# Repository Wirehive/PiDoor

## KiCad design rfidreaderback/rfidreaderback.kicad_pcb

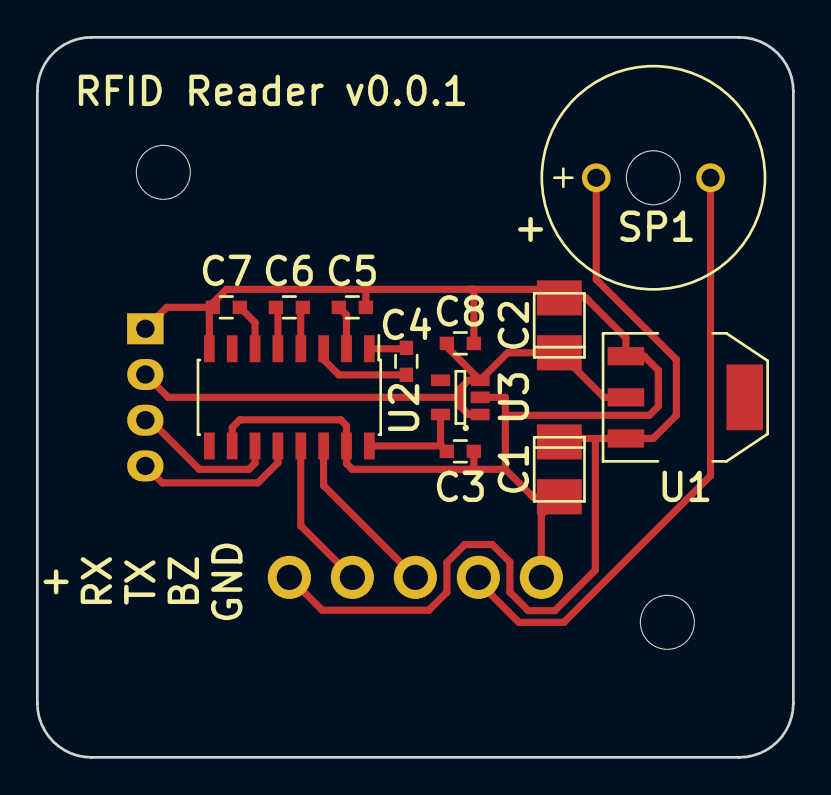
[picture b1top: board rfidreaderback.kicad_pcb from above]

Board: 2 copper layers, 42.0 x 40.0 mm, 14 parts (1 on the bottom side), 15 nets.

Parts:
C1, C2: 22µ; TantalC_SizeT_EIA-3528
C3, C4, C5, C6, C7, C8: 1µ; C_0603
P1: READER; Socket_Strip_Straight_1x04
P2: PI; 3_5mm_terminal_1x05
SP1: MCABI-020-RC; MagneticBuzzer_ProSignal_ABT-410-RC
U1: LD1117S50TR; SOT-223
U2: ST3232BDR; SOIC-16_3.9x9.9mm_Pitch1.27mm
U3: MIC5317-3.3YM5; SOT-23-5

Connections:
+3V3: C3.2, U2.16, U3.VO
+5V: C2.1, C8.2, P1.2, U1.VO, U3.VI
+12V: C1.1, P2.5, SP1.2, U1.VI
/EIA-RX: P2.4, U2.13
/EIA-TX: P2.3, U2.14
/RXD: P1.4, U2.12
/TXD: P1.3, U2.11
/buzzer: P2.2, SP1.1
GND: C1.2, C2.2, C3.1, C5.1, C7.1, C8.1, P1.1, P2.1, U1.GND, U2.8, U2.10, U2.15, U3.GND
unnamed: C4.1, U2.1
unnamed: C4.2, U2.3
unnamed: C5.2, U2.2
unnamed: C6.1, U2.4
unnamed: C6.2, U2.5
unnamed: C7.2, U2.6

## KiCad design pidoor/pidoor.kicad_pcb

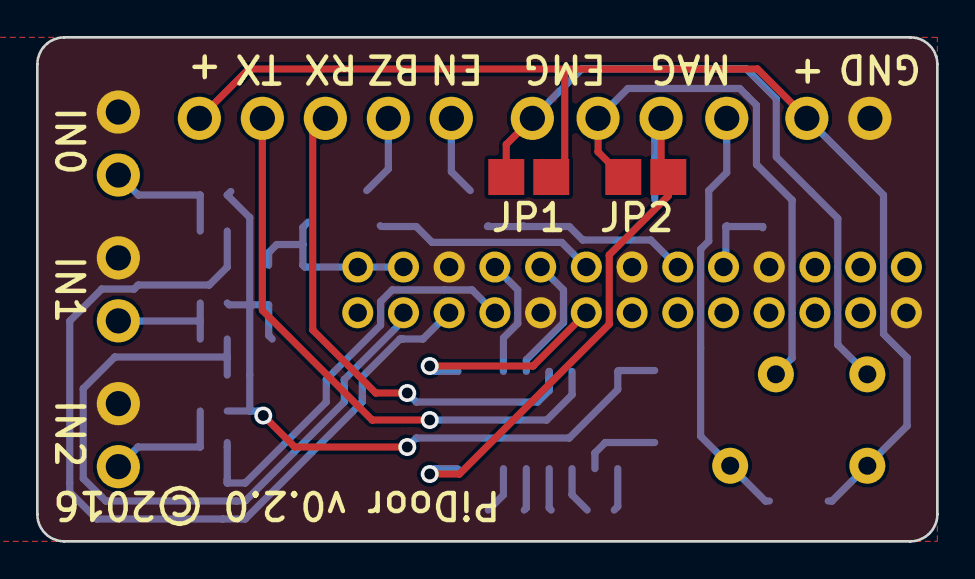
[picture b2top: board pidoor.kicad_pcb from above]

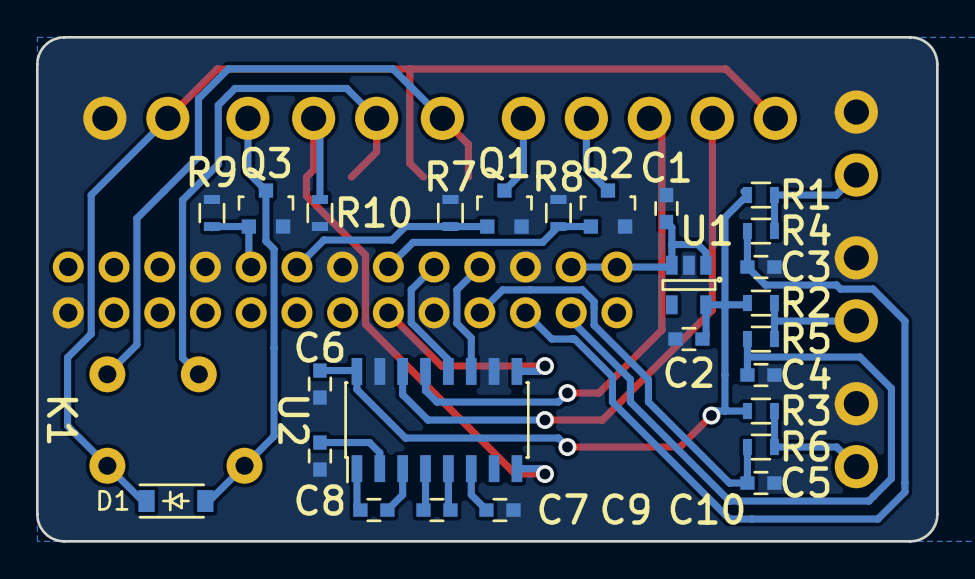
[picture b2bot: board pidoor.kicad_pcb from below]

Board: 2 copper layers, 50.0 x 28.0 mm, 36 parts (34 on the bottom side), 30 nets.

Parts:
C1, C2, C3, C4, C5, C6, C7, C8, C9, C10: 1µ; C_0603
D1: D_Small; SOD-123
JP1, JP2: JUMPER; SMD_Jumper
K1: RELAY_G6L; Relay_G6L
P1: CONN_02X13; Socket_Strip_Straight_2x13
P2: PWR; 3_5mm_terminal_1x02
P3: IN0; 3_5mm_terminal_1x02
P4: IN1; 3_5mm_terminal_1x02
P5: IN2; 3_5mm_terminal_1x02
P6: READER; 3_5mm_terminal_1x05
P7: MAG; 3_5mm_terminal_1x04
Q1, Q2, Q3: PMV16XN; SOT-23
R1, R2, R3: 4K7; R_0603
R4, R5, R6, R7, R8, R9, R10: 4k7; R_0603
U1: MIC5317-3.3YM5; MIC5317
U2: ST3232BDR; SOIC-16_3.9x9.9mm_Pitch1.27mm

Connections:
+3V3: C2.1, C6.2, R1.1, R2.1, R3.1, U1.VO, U2.16
+5V: C1.1, P1.2, P1.4, U1.VI
+12V: D1.1, JP1.2, K1.5, P2.2, P6.5
/12_EMG: JP2.2, P7.2, R10.1, U2.8
/BUZZER: P1.12, Q2.1, R8.1
/EIA-RX: P6.3, U2.13
/EIA-TX: P6.4, U2.14
/EMG: P1.11, U2.9
/EN_READ: P1.16, Q1.1, R7.1
/IN0: C3.1, P1.5, R4.1
/IN1: C4.1, P1.3, R5.1
/IN2: C5.1, P1.7, R6.1
/MAG: P1.18, Q3.1, R9.1
/RXD: P1.10, U2.12
/TXD: P1.8, U2.11
GND: C1.2, C2.2, C3.2, C4.2, C5.2, C6.1, C8.1, C10.1, P1.6, P1.9, P1.14, P1.20, P1.25, P2.1, P3.1, P4.1, P5.1, Q1.2, Q2.2, Q3.2, R7.2, R8.2, R9.2, R10.2, U1.GND, U2.10, U2.15
unnamed: C7.1, U2.1
unnamed: C7.2, U2.3
unnamed: C8.2, U2.2
unnamed: C9.1, U2.4
unnamed: C9.2, U2.5
unnamed: C10.2, U2.6
unnamed: D1.2, K1.8, P7.1, Q3.3
unnamed: JP1.1, K1.4, P7.4
unnamed: JP2.1, K1.2, P7.3
unnamed: P3.2, R1.2, R4.2
unnamed: P4.2, R2.2, R5.2
unnamed: P5.2, R3.2, R6.2
unnamed: P6.1, Q1.3
unnamed: P6.2, Q2.3

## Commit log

2016-09-28 door electronics
2016-09-29 v0.0.1
2016-09-30 RFID back
2016-09-30 license
2016-10-03 Probably best if the level converters are connected to the correct level
2016-10-03 relay for AC strikers
2016-10-03 previews
2016-10-03 switch unnecisarry milling to drill
2016-10-04 ascii really
2016-10-06 gnd unused inputs
2016-10-25 pre-production tweeks
2016-10-31 Pi's pin 1 and 2 have strong pullups so we don't want more, or to create a divider; Mag collaps blows MosFETs, prodect with at least a MOV

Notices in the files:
pidoor/pidoor.kicad_pcb:
©2016 Wirehive ltd, CC BY-SA
PiDoor v0.2.0 ©2016
